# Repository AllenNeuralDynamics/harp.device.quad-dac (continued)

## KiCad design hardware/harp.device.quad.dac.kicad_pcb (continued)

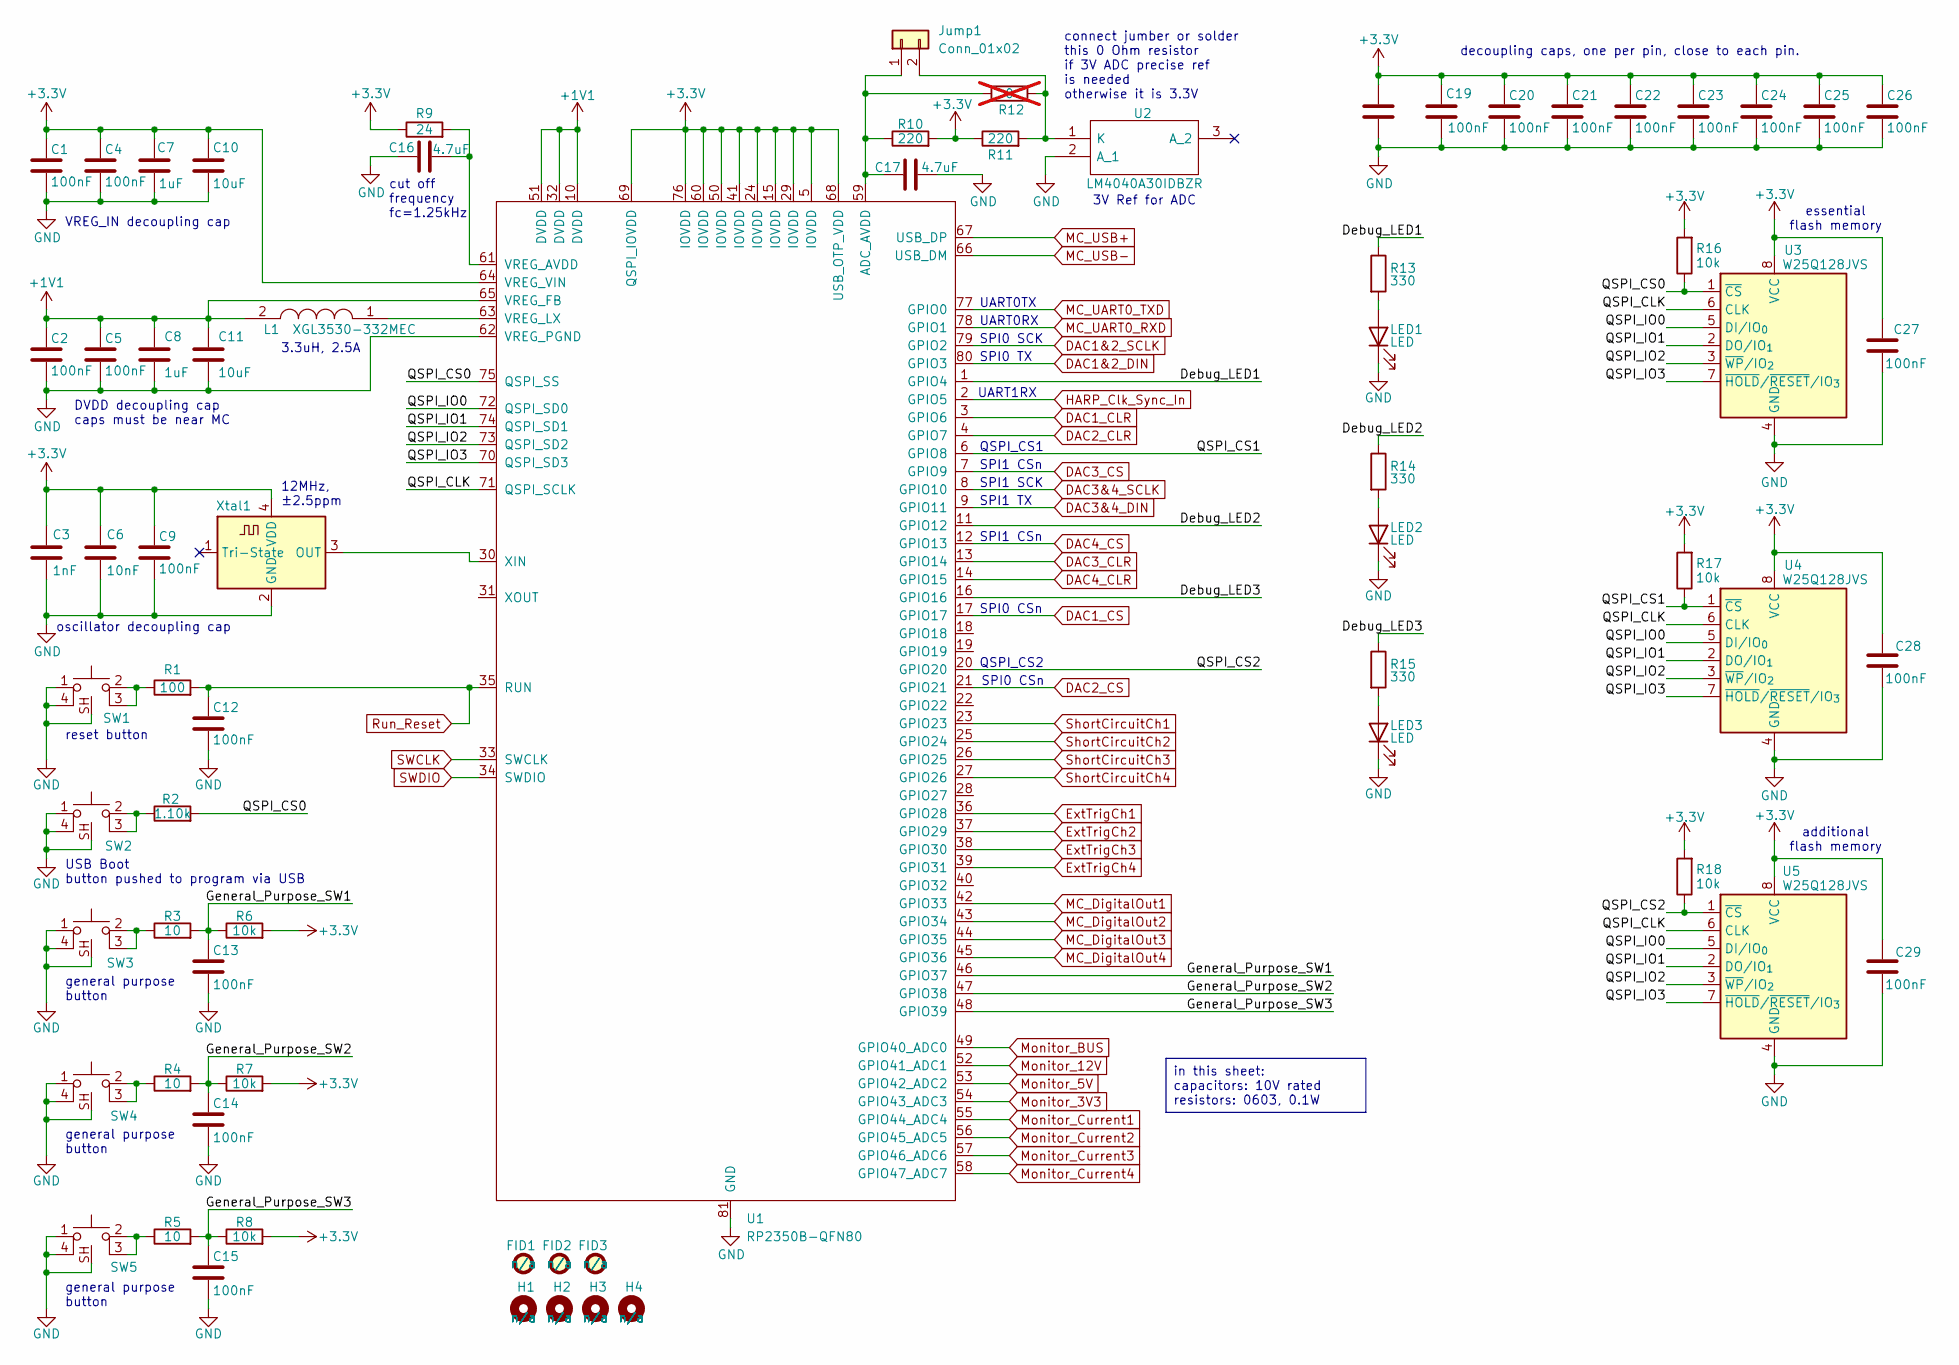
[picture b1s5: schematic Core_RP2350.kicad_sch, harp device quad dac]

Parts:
C1, C2, C4, C5, C9, C12, C13, C14, C15, C19, C20, C21, C22, C23, C24, C25, C26, C27, C28, C29: 100nF; C_0603_1608Metric; Rated Voltage 50V; Tolerance 10%; Manufacturer_Part_Number C0603C104K5RACTU
C3: 1nF; C_0603_1608Metric; Rated Voltage 50V; Tolerance 10%; Manufacturer_Part_Number C0603C102K5RACTU
C6: 10nF; C_0603_1608Metric; Rated Voltage 50V; Tolerance 10%; Manufacturer_Part_Number C0603C103K5RACTU
C7, C8: 1uF; C_0603_1608Metric; Rated Voltage 50V; Tolerance 10%; Manufacturer_Part_Number C1608X7R1H105K080AB
C10, C11, C18: 10uF; C_0603_1608Metric; Rated Voltage 25V; Tolerance 10%; Manufacturer_Part_Number GRM188R61E106KA73D
C16, C17: 4.7uF; C_0603_1608Metric; Rated Voltage 35V; Tolerance 10%; Manufacturer_Part_Number C1608X5R1V475K080AC
FID1, FID2, FID3: Fiducial; Fiducial_0.5mm_Mask1mm; Manufacturer_Part_Number n/a
H1, H2, H3, H4: MountingHole_Pad; MountingHole_3.2mm_M3_DIN965; Manufacturer_Part_Number n/a
Jump1: Conn_01x02; PinHeader_1x02_P2.54mm_Vertical; MPN M20-9990246
L1: XGL3530-332MEC; XGL3530332MEC; Manufacturer_Part_Number XGL3530-332MEC
LED1, LED2, LED3: LED; LED_0603_1608Metric_Pad1.05x0.95mm_HandSolder; MPN XZCDGK53W-1VF
R1: 100; R_0603_1608Metric; Tolerance 1%; MPN AC0603FR-13100RL
R2: 1.10k; R_0603_1608Metric; Tolerance 0.1%; MPN RT0603BRD071K1L
R3, R4, R5: 10; R_0603_1608Metric; Tolerance 1%; MPN AC0603FR-1310RL
R6, R7, R8, R16, R17, R18: 10k; R_0603_1608Metric; Tolerance 0.1%; MPN RT0603BRD0710KL
R9: 24; R_0603_1608Metric; Tolerance 1%; MPN AC0603FR-0724RL
R10, R11: 220; R_0603_1608Metric; Tolerance 1%; MPN RC0603FR-07220RL
R12: 0; R_0603_1608Metric; MPN RC0603JR-070RL; not fitted
R13, R14, R15: 330; R_0603_1608Metric; Tolerance 1%; MPN RC0603FR-07330RL
SW1, SW2, SW3, SW4, SW5: SW_Push_1P1T-SH_NO_Vertical_Wuerth_WS-TASV; MPN 435451019820
U1: RP2350B-QFN80; RP2350B_QFN-80_EP_10.573x10.573_Pitch0.4mm; MPN SC1510-A4
U2: LM4040A30IDBZR; SOT95P237X112-3N; Manufacturer_Part_Number LM4040A30IDBZR; Mouser Part Number 595-LM4040A30IDBZR
U3, U4, U5: W25Q128JVS; SOIC-8_5.3x5.3mm_P1.27mm
Xtal1: ECS-TXO-2016; Crystal_SMD_2016-4Pin_2.0x1.6mm; Tolerance ±2.5ppm; MPN ECS-TXO-2016-33-120-TR

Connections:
+1V1: C2.2, C5.2, C8.1, C11.1, L1.2, U1.10 (DVDD), U1.32 (DVDD), U1.51 (DVDD), U1.65 (VREG_FB)
+3.3V: C1.2, C3.2, C4.2, C6.2, C7.1, C9.2, C10.1, C18.1, C19.2, C20.2, C21.2, C22.2, C23.2, C24.2, C25.2, C26.2, C27.2, C28.2, C29.2, R6.2, R7.2, R8.2, R9.1, R10.2, R11.1, R16.2, R17.2, R18.2, U1.5 (IOVDD), U1.15 (IOVDD), U1.24 (IOVDD), U1.29 (IOVDD), U1.41 (IOVDD), U1.50 (IOVDD), U1.60 (IOVDD), U1.64 (VREG_VIN), U1.68 (USB_OTP_VDD), U1.69 (QSPI_IOVDD), U1.76 (IOVDD), U3.8 (VCC), U4.8 (VCC), U5.8 (VCC), Xtal1.4 (VDD); also elsewhere on the board
/Core_RP2350/Debug_LED1: R13.1, U1.1 (GPIO4)
/Core_RP2350/Debug_LED2: R14.1, U1.11 (GPIO12)
/Core_RP2350/Debug_LED3: R15.1, U1.16 (GPIO16)
/Core_RP2350/General_Purpose_SW1: C13.2, R3.2, R6.1, U1.46 (GPIO37)
/Core_RP2350/General_Purpose_SW2: C14.2, R4.2, R7.1, U1.47 (GPIO38)
/Core_RP2350/General_Purpose_SW3: C15.2, R5.2, R8.1, U1.48 (GPIO39)
/Core_RP2350/QSPI_CLK: U1.71 (QSPI_SCLK), U3.6 (CLK), U4.6 (CLK), U5.6 (CLK)
/Core_RP2350/QSPI_CS0: R2.2, R16.1, U1.75 (QSPI_SS), U3.1 (~CS)
/Core_RP2350/QSPI_CS1: R17.1, U1.6 (GPIO8), U4.1 (~CS)
/Core_RP2350/QSPI_CS2: R18.1, U1.20 (GPIO20), U5.1 (~CS)
/Core_RP2350/QSPI_IO0: U1.72 (QSPI_SD0), U3.5 (DI/IO_{0}), U4.5 (DI/IO_{0}), U5.5 (DI/IO_{0})
/Core_RP2350/QSPI_IO1: U1.74 (QSPI_SD1), U3.2 (DO/IO_{1}), U4.2 (DO/IO_{1}), U5.2 (DO/IO_{1})
/Core_RP2350/QSPI_IO2: U1.73 (QSPI_SD2), U3.3 (~WP/IO_{2}), U4.3 (~WP/IO_{2}), U5.3 (~WP/IO_{2})
/Core_RP2350/QSPI_IO3: U1.70 (QSPI_SD3), U3.7 (~HOLD/~RESET/IO_{3}), U4.7 (~HOLD/~RESET/IO_{3}), U5.7 (~HOLD/~RESET/IO_{3})
DAC1&2_DIN: U1.80 (GPIO3); also elsewhere on the board
DAC1&2_SCLK: U1.79 (GPIO2); also elsewhere on the board
DAC1_CLR: U1.3 (GPIO6); also elsewhere on the board
DAC1_CS: U1.17 (GPIO17); also elsewhere on the board
DAC2_CLR: U1.4 (GPIO7); also elsewhere on the board
DAC2_CS: U1.21 (GPIO21); also elsewhere on the board
DAC3&4_DIN: U1.9 (GPIO11); also elsewhere on the board
DAC3&4_SCLK: U1.8 (GPIO10); also elsewhere on the board
DAC3_CLR: U1.13 (GPIO14); also elsewhere on the board
DAC3_CS: U1.7 (GPIO9); also elsewhere on the board
DAC4_CLR: U1.14 (GPIO15); also elsewhere on the board
DAC4_CS: U1.12 (GPIO13); also elsewhere on the board
ExtTrigCh1: U1.36 (GPIO28); also elsewhere on the board
ExtTrigCh2: U1.37 (GPIO29); also elsewhere on the board
ExtTrigCh3: U1.38 (GPIO30); also elsewhere on the board
ExtTrigCh4: U1.39 (GPIO31); also elsewhere on the board
GND: C1.1, C2.1, C3.1, C4.1, C5.1, C6.1, C7.2, C8.2, C9.1, C10.2, C11.2, C12.1, C13.1, C14.1, C15.1, C16.1, C17.2, C18.2, C19.1, C20.1, C21.1, C22.1, C23.1, C24.1, C25.1, C26.1, C27.1, C28.1, C29.1, LED1.1 (K), LED2.1 (K), LED3.1 (K), SW1.1, SW1.4, SW1.SH, SW2.1, SW2.4, SW2.SH, SW3.1, SW3.4, SW3.SH, SW4.1, SW4.4, SW4.SH, SW5.1, SW5.4, SW5.SH, U1.62 (VREG_PGND), U1.81 (GND), U2.2 (A_1), U3.4 (GND), U4.4 (GND), U5.4 (GND), Xtal1.2 (GND); also elsewhere on the board
HARP_Clk_Sync_In: U1.2 (GPIO5); also elsewhere on the board
MC_DigitalOut1: U1.42 (GPIO33); also elsewhere on the board
MC_DigitalOut2: U1.43 (GPIO34); also elsewhere on the board
MC_DigitalOut3: U1.44 (GPIO35); also elsewhere on the board
MC_DigitalOut4: U1.45 (GPIO36); also elsewhere on the board
MC_UART0_RXD: U1.78 (GPIO1); also elsewhere on the board
MC_UART0_TXD: U1.77 (GPIO0); also elsewhere on the board
MC_USB+: U1.67 (USB_DP); also elsewhere on the board
MC_USB-: U1.66 (USB_DM); also elsewhere on the board
Monitor_3V3: U1.54 (GPIO43_ADC3); also elsewhere on the board
Monitor_5V: U1.53 (GPIO42_ADC2); also elsewhere on the board
Monitor_12V: U1.52 (GPIO41_ADC1); also elsewhere on the board
Monitor_BUS: U1.49 (GPIO40_ADC0); also elsewhere on the board
Monitor_Current1: U1.55 (GPIO44_ADC4); also elsewhere on the board
Monitor_Current2: U1.56 (GPIO45_ADC5); also elsewhere on the board
Monitor_Current3: U1.57 (GPIO46_ADC6); also elsewhere on the board
Monitor_Current4: U1.58 (GPIO47_ADC7); also elsewhere on the board
unnamed: C17.1, Jump1.1, R10.1, R12.1, U1.59 (ADC_AVDD)
unnamed: Jump1.2, R11.2, R12.2, U2.1 (K)
unnamed: LED1.2 (A), R13.2
unnamed: LED2.2 (A), R14.2
unnamed: LED3.2 (A), R15.2
unnamed: R1.1, SW1.2, SW1.3
unnamed: R2.1, SW2.2, SW2.3
unnamed: R3.1, SW3.2, SW3.3
unnamed: R4.1, SW4.2, SW4.3
unnamed: R5.1, SW5.2, SW5.3
unnamed: C16.2, R9.2, U1.61 (VREG_AVDD)
unnamed: L1.1, U1.63 (VREG_LX)
unnamed: U1.30 (XIN), Xtal1.3 (OUT)
Run_Reset: C12.2, R1.2, U1.35 (RUN); also elsewhere on the board
SWCLK: U1.33 (SWCLK); also elsewhere on the board
SWDIO: U1.34 (SWDIO); also elsewhere on the board
ShortCircuitCh1: U1.23 (GPIO23); also elsewhere on the board
ShortCircuitCh2: U1.25 (GPIO24); also elsewhere on the board
ShortCircuitCh3: U1.26 (GPIO25); also elsewhere on the board
ShortCircuitCh4: U1.27 (GPIO26); also elsewhere on the board

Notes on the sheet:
SPI0 CSn
decoupling caps, one per pin, close to each pin.
reset button
general purpose button
3V Ref for ADC
UART0RX
UART1RX
DVDD decoupling cap caps must be near MC
USB Boot button pushed to program via USB
SPI0 SCK
3.3uH, 2.5A
SPI1 SCK
VREG_IN decoupling cap
additional flash memory
connect jumber or solder this 0 Ohm resistor if 3V ADC precise ref is needed otherwise it is 3.3V
SPI1 CSn
essential flash memory
QSPI_CS2
cut off frequency fc=1.25kHz
SPI0 TX
SPI1 TX
oscillator decoupling cap
UART0TX
12MHz, ±2.5ppm
QSPI_CS1
in this sheet: capacitors: 10V rated resistors: 0603, 0.1W

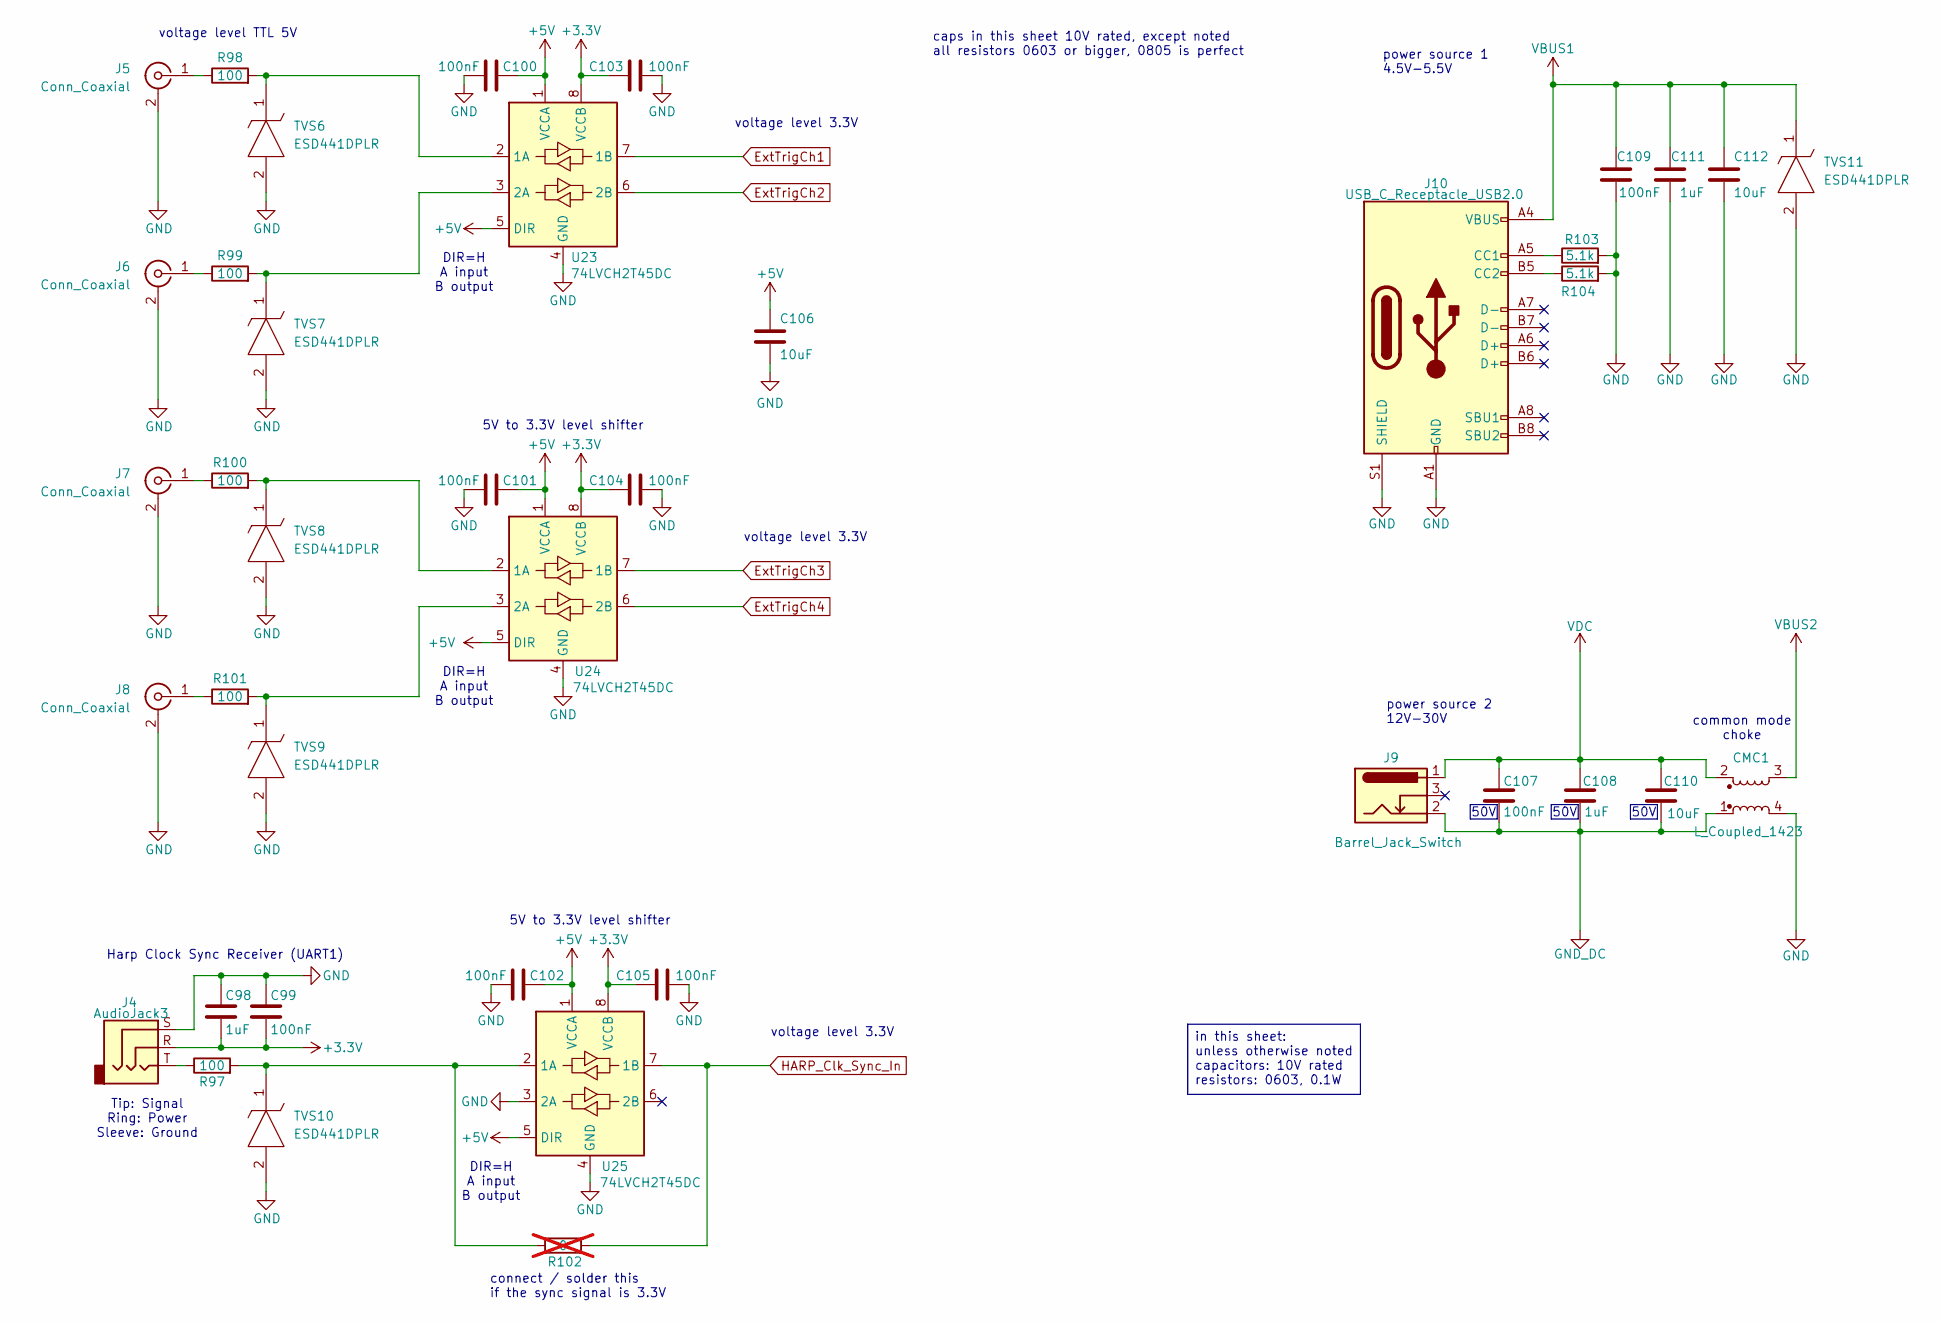
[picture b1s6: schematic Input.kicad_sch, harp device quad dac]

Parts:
C98, C108, C111: 1uF; C_0603_1608Metric; Rated Voltage 50V; Tolerance 10%; Manufacturer_Part_Number C1608X7R1H105K080AB
C99, C100, C101, C102, C103, C104, C105, C107, C109: 100nF; C_0603_1608Metric; Rated Voltage 50V; Tolerance 10%; Manufacturer_Part_Number C0603C104K5RACTU
C106, C110, C112: 10uF; C_0603_1608Metric; Rated Voltage 25V; Tolerance 10%; Manufacturer_Part_Number GRM188R61E106KA73D
CMC1: L_Coupled_1423; L_CommonModeChoke_TDKCorporation_1210
J4: AudioJack3; Jack_3.5mm_CUI_SJ-3524-SMT_Horizontal; Manufacturer_Part_Number SJ-3524-SMT-TR-BE
J5, J6, J7, J8: Conn_Coaxial; SMA_TE_Connectivity_CONSMA002-SMD-G-T_Horizontal; MPN CONSMA002-SMD-G-T
J9: Barrel_Jack_Switch; BarrelJack_CUI_PJ-102AH_Horizontal; Manufacturer_Part_Number PJ-102AH
J10: USB_C_Receptacle_USB2.0; USB_C_Receptacle_JAE_DX07S016JA1R1500; Manufacturer_Part_Number DX07S016JA1R1500
R97, R98, R99, R100, R101: 100; R_0603_1608Metric; Tolerance 1%; MPN AC0603FR-13100RL
R102: 0; R_0603_1608Metric; MPN RC0603JR-070RL; not fitted
R103, R104: 5.1k; R_0603_1608Metric; Tolerance 1%; MPN RC0603FR-075K1L
TVS6, TVS7, TVS8, TVS9, TVS10, TVS11: ESD441DPLR; Manufacturer_Part_Number ESD441DPLR; Mouser Part Number 595-ESD441DPLR
U23, U24, U25: 74LVCH2T45DC; VSSOP-8_2.3x2mm_P0.5mm

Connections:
+3.3V: C98.2, C99.1, C103.2, C104.2, C105.2, J4.R, U23.8 (VCCB), U24.8 (VCCB), U25.8 (VCCB); also elsewhere on the board
+5V: C100.1, C101.1, C102.1, C106.1, U23.1 (VCCA), U23.5 (DIR), U24.1 (VCCA), U24.5 (DIR), U25.1 (VCCA), U25.5 (DIR); also elsewhere on the board
ExtTrigCh1: U23.7 (1B); also elsewhere on the board
ExtTrigCh2: U23.6 (2B); also elsewhere on the board
ExtTrigCh3: U24.7 (1B); also elsewhere on the board
ExtTrigCh4: U24.6 (2B); also elsewhere on the board
GND: C98.1, C99.2, C100.2, C101.2, C102.2, C103.1, C104.1, C105.1, C106.2, C109.1, C111.2, C112.2, CMC1.4, J4.S, J5.2 (Ext), J6.2 (Ext), J7.2 (Ext), J8.2 (Ext), J10.A1 (GND), J10.A12 (GND), J10.B1 (GND), J10.B12 (GND), J10.S1 (SHIELD), R103.2, R104.2, TVS6.2, TVS7.2, TVS8.2, TVS9.2, TVS10.2, TVS11.2, U23.4 (GND), U24.4 (GND), U25.3 (2A), U25.4 (GND); also elsewhere on the board
GND_DC: C107.1, C108.2, C110.2, CMC1.1, J9.2
HARP_Clk_Sync_In: R102.2, U25.7 (1B); also elsewhere on the board
unnamed: J4.T, R97.1
unnamed: J5.1 (In), R98.1
unnamed: J6.1 (In), R99.1
unnamed: J7.1 (In), R100.1
unnamed: J8.1 (In), R101.1
unnamed: J10.A5 (CC1), R103.1
unnamed: J10.B5 (CC2), R104.1
unnamed: R98.2, TVS6.1, U23.2 (1A)
unnamed: R99.2, TVS7.1, U23.3 (2A)
unnamed: R100.2, TVS8.1, U24.2 (1A)
unnamed: R101.2, TVS9.1, U24.3 (2A)
unnamed: R97.2, R102.1, TVS10.1, U25.2 (1A)
VBUS1: C109.2, C111.1, C112.1, J10.A4 (VBUS), J10.A9 (VBUS), J10.B4 (VBUS), J10.B9 (VBUS), TVS11.1; also elsewhere on the board
VBUS2: CMC1.3; also elsewhere on the board
VDC: C107.2, C108.1, C110.1, CMC1.2, J9.1

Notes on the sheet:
5V to 3.3V level shifter
connect / solder this if the sync signal is 3.3V
voltage level 3.3V
caps in this sheet 10V rated, except noted all resistors 0603 or bigger, 0805 is perfect
power source 1 4.5V-5.5V
voltage level TTL 5V
common mode choke
Tip: Signal Ring: Power Sleeve: Ground
power source 2 12V-30V
DIR=H A input B output
Harp Clock Sync Receiver (UART1)
in this sheet: unless otherwise noted capacitors: 10V rated resistors: 0603, 0.1W
50V

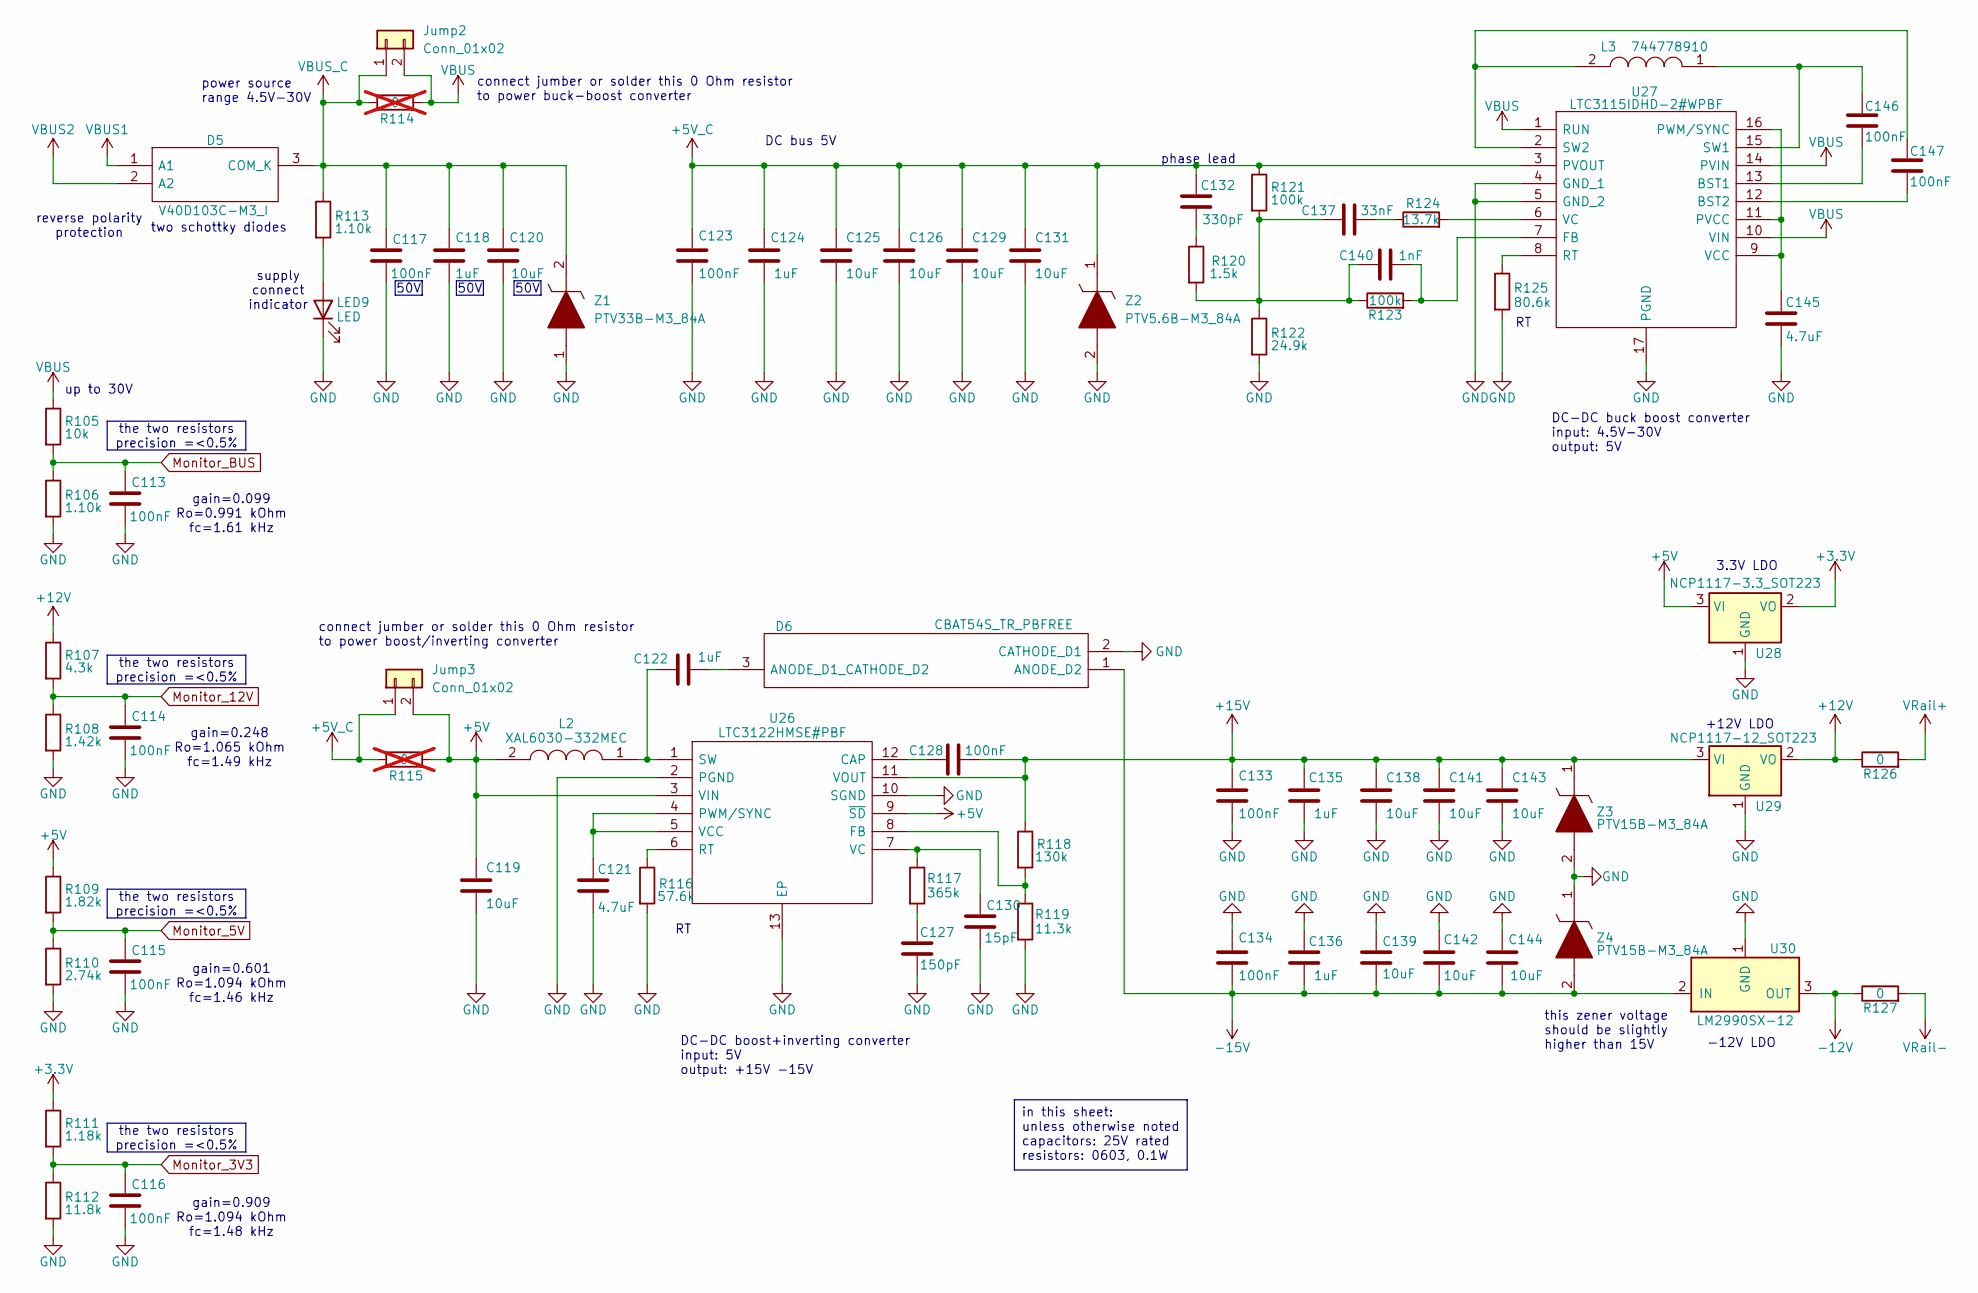
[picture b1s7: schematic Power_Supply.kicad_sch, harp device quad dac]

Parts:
C113, C114, C115, C116, C117, C123, C128, C133, C134, C146, C147: 100nF; C_0603_1608Metric; Rated Voltage 50V; Tolerance 10%; Manufacturer_Part_Number C0603C104K5RACTU
C118, C122, C124, C135, C136: 1uF; C_0603_1608Metric; Rated Voltage 50V; Tolerance 10%; Manufacturer_Part_Number C1608X7R1H105K080AB
C119, C125, C126, C129, C131, C138, C139, C141, C142, C143, C144: 10uF; C_0603_1608Metric; Rated Voltage 25V; Tolerance 10%; Manufacturer_Part_Number GRM188R61E106KA73D
C120: 10uF; C_1206_3216Metric; Rated Voltage 50V; Tolerance 10%; Manufacturer_Part_Number C3216X7R1H106K160AC
C121, C145: 4.7uF; C_0603_1608Metric; Rated Voltage 35V; Tolerance 10%; Manufacturer_Part_Number C1608X5R1V475K080AC
C127: 150pF; C_0603_1608Metric; Rated Voltage 50V; Tolerance 10%; Manufacturer_Part_Number C0603C151K5RACTU
C130: 15pF; C_0603_1608Metric; Rated Voltage 50V; Tolerance 10%; Manufacturer_Part_Number C0603C150K5RACTU
C132: 330pF; C_0603_1608Metric; Rated Voltage 50V; Tolerance 10%; Manufacturer_Part_Number C0603C331K5RACTU
C137: 33nF; C_0603_1608Metric; Rated Voltage 50V; Tolerance 10%; Manufacturer_Part_Number C0603C333K5RACTU
C140: 1nF; C_0603_1608Metric; Rated Voltage 50V; Tolerance 10%; Manufacturer_Part_Number C0603C102K5RACTU
D5: V40D103C-M3_I; V40D103CM3I; Manufacturer_Part_Number V40D103C-M3/I; Mouser Part Number 78-V40D103C-M3/I
D6: CBAT54S_TR_PBFREE; SOT95P230X109-3N; Manufacturer_Part_Number CBAT54S TR PBFREE; Mouser Part Number 610-CBAT54STR
Jump2, Jump3: Conn_01x02; PinHeader_1x02_P2.54mm_Vertical; MPN M20-9990246
L2: XAL6030-332MEC; XAL6030182MEB; Manufacturer_Part_Number XAL6030-332MEC; Mouser Part Number 994-XAL6030-332MEC
L3: 744778910; WE-PD_7332-7345_PLASTIC_BASE54; Manufacturer_Part_Number 744778910; Mouser Part Number 710-744778910
LED9: LED; LED_0603_1608Metric_Pad1.05x0.95mm_HandSolder; MPN XZCDGK53W-1VF
R105: 10k; R_0603_1608Metric; Tolerance 0.1%; MPN RT0603BRD0710KL
R106, R113: 1.10k; R_0603_1608Metric; Tolerance 0.1%; MPN RT0603BRD071K1L
R107: 4.3k; R_0603_1608Metric; Tolerance 0.1%; MPN RT0603BRD074K3L
R108: 1.42k; R_0603_1608Metric; Tolerance 0.1%; MPN RT0603BRD071K42L
R109: 1.82k; R_0603_1608Metric; Tolerance 0.1%; MPN RT0603BRD071K82L
R110: 2.74k; R_0603_1608Metric; Tolerance 0.1%; MPN RT0603BRD072K74L
R111: 1.18k; R_0603_1608Metric; Tolerance 0.1%; MPN RT0603BRD071K18L
R112: 11.8k; R_0603_1608Metric; Tolerance 0.1%; MPN RT0603BRD0711K8L
R114, R115: 0; R_0603_1608Metric; MPN RC0603JR-070RL; not fitted
R116: 57.6k; R_0603_1608Metric; Tolerance 1%; MPN RC0603FR-0757K6L
R117: 365k; R_0603_1608Metric; Tolerance 1%; MPN RC0603FR-07365KL
R118: 130k; R_0603_1608Metric; Tolerance 1%; MPN AC0603FR-07130KL
R119: 11.3k; R_0603_1608Metric; Tolerance 1%; MPN RC0603FR-0711K3L
R120: 1.5k; R_0603_1608Metric; Tolerance 1%; MPN RC0603FR-071K5L
R121, R123: 100k; R_0603_1608Metric; Tolerance 1%; MPN RC0603FR-07100KL
R122: 24.9k; R_0603_1608Metric; Tolerance 1%; MPN RC0603FR-0724K9L
R124: 13.7k; R_0603_1608Metric; Tolerance 1%; MPN AC0603FR-0713K7L
R125: 80.6k; R_0603_1608Metric; Tolerance 1%; MPN RC0603FR-0780K6L
R126, R127: 0; R_0603_1608Metric; MPN RC0603JR-070RL
U26: LTC3122HMSE#PBF; SOP65P490X110-13N; Manufacturer_Part_Number LTC3122HMSE#PBF; Mouser Part Number 584-LTC3122HMSE#PBF
U27: LTC3115IDHD-2#WPBF; SON50P400X500X80-17N-D; Manufacturer_Part_Number LTC3115IDHD-2#WPBF
U28: NCP1117-3.3_SOT223; SOT-223-3_TabPin2
U29: NCP1117-12_SOT223; SOT-223-3_TabPin2
U30: LM2990SX-12; KTT0003B
Z1: PTV33B-M3_84A; PTV47BM384A; Manufacturer_Part_Number PTV33B-M3/84A; Mouser Part Number 625-PTV33B-M3/84A
Z2: PTV5.6B-M3_84A; PTV47BM384A; Manufacturer_Part_Number PTV5.6B-M3/84A; Mouser Part Number 625-PTV5.6B-M3/84A
Z3, Z4: PTV15B-M3_84A; PTV47BM384A; Manufacturer_Part_Number PTV15B-M3/84A; Mouser Part Number 625-PTV15B-M3/84A

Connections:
+3.3V: R111.1, U28.2 (VO); also elsewhere on the board
+5V: C119.1, Jump3.2, L2.2, R109.1, R115.2, U26.3 (VIN), U26.9 (~SD), U28.3 (VI); also elsewhere on the board
+5V_C: C123.1, C124.1, C125.1, C126.1, C129.1, C131.1, C132.1, Jump3.1, R115.1, R121.1, U27.3 (PVOUT), Z2.1
+12V: R107.1, R126.1, U29.2 (VO)
+15V: C128.1, C133.1, C135.1, C138.1, C141.1, C143.1, R118.1, U26.11 (VOUT), U29.3 (VI), Z3.1
-12V: R127.1, U30.3 (OUT)
-15V: C134.2, C136.2, C139.2, C142.2, C144.2, D6.1 (ANODE_D2), U30.2 (IN), U30.4 (IN), U30.5 (IN), U30.6 (IN), Z4.2
GND: C113.1, C114.1, C115.1, C116.1, C117.1, C118.2, C119.2, C120.2, C121.2, C123.2, C124.2, C125.2, C126.2, C127.1, C129.2, C130.1, C131.2, C133.2, C134.1, C135.2, C136.1, C138.2, C139.1, C141.2, C142.1, C143.2, C144.1, C145.2, D6.2 (CATHODE_D1), LED9.1 (K), R106.2, R108.2, R110.2, R112.2, R116.2, R119.2, R122.2, R125.2, U26.2 (PGND), U26.10 (SGND), U26.13 (EP), U27.4 (GND_1), U27.5 (GND_2), U27.17 (PGND), U28.1 (GND), U29.1 (GND), U30.1 (GND), Z1.1, Z2.2, Z3.2, Z4.1; also elsewhere on the board
Monitor_3V3: C116.2, R111.2, R112.1; also elsewhere on the board
Monitor_5V: C115.2, R109.2, R110.1; also elsewhere on the board
Monitor_12V: C114.2, R107.2, R108.1; also elsewhere on the board
Monitor_BUS: C113.2, R105.2, R106.1; also elsewhere on the board
unnamed: C127.2, R117.2
unnamed: C132.2, R120.1
unnamed: C137.1, R124.1
unnamed: C137.2, C140.2, R120.2, R121.2, R122.1, R123.1
unnamed: C122.2, D6.3 (ANODE_D1_CATHODE_D2)
unnamed: LED9.2 (A), R113.2
unnamed: C128.2, U26.12 (CAP)
unnamed: R118.2, R119.1, U26.8 (FB)
unnamed: C121.1, U26.4 (PWM/SYNC), U26.5 (VCC)
unnamed: R116.1, U26.6 (RT)
unnamed: C122.1, L2.1, U26.1 (SW)
unnamed: C130.2, R117.1, U26.7 (VC)
unnamed: C146.1, U27.13 (BST1)
unnamed: C147.1, U27.12 (BST2)
unnamed: C140.1, R123.2, U27.7 (FB)
unnamed: C145.1, U27.9 (VCC), U27.11 (PVCC), U27.16 (PWM/SYNC)
unnamed: R125.1, U27.8 (RT)
unnamed: C146.2, L3.1, U27.15 (SW1)
unnamed: C147.2, L3.2, U27.2 (SW2)
unnamed: R124.2, U27.6 (VC)
VBUS: Jump2.2, R105.1, R114.2, U27.1 (RUN), U27.10 (VIN), U27.14 (PVIN)
VBUS1: D5.1 (A1); also elsewhere on the board
VBUS2: D5.2 (A2); also elsewhere on the board
VBUS_C: C117.2, C118.1, C120.1, D5.3 (COM_K), Jump2.1, R113.1, R114.1, Z1.2
VRail+: R126.2; also elsewhere on the board
VRail-: R127.2; also elsewhere on the board

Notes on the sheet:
this zener voltage should be slightly higher than 15V
supply connect indicator
+12V LDO
up to 30V
-12V LDO
3.3V LDO
phase lead
gain=0.909 Ro=1.094 kOhm fc=1.48 kHz
reverse polarity protection
DC-DC buck boost converter input: 4.5V-30V output: 5V
two schottky diodes
gain=0.601 Ro=1.094 kOhm fc=1.46 kHz
gain=0.248 Ro=1.065 kOhm fc=1.49 kHz
connect jumber or solder this 0 Ohm resistor to power boost/inverting converter
connect jumber or solder this 0 Ohm resistor to power buck-boost converter
DC-DC boost+inverting converter input: 5V output: +15V -15V
DC bus 5V
gain=0.099 Ro=0.991 kOhm fc=1.61 kHz
power source range 4.5V-30V
in this sheet: unless otherwise noted capacitors: 25V rated resistors: 0603, 0.1W
50V
the two resistors precision =<0.5%

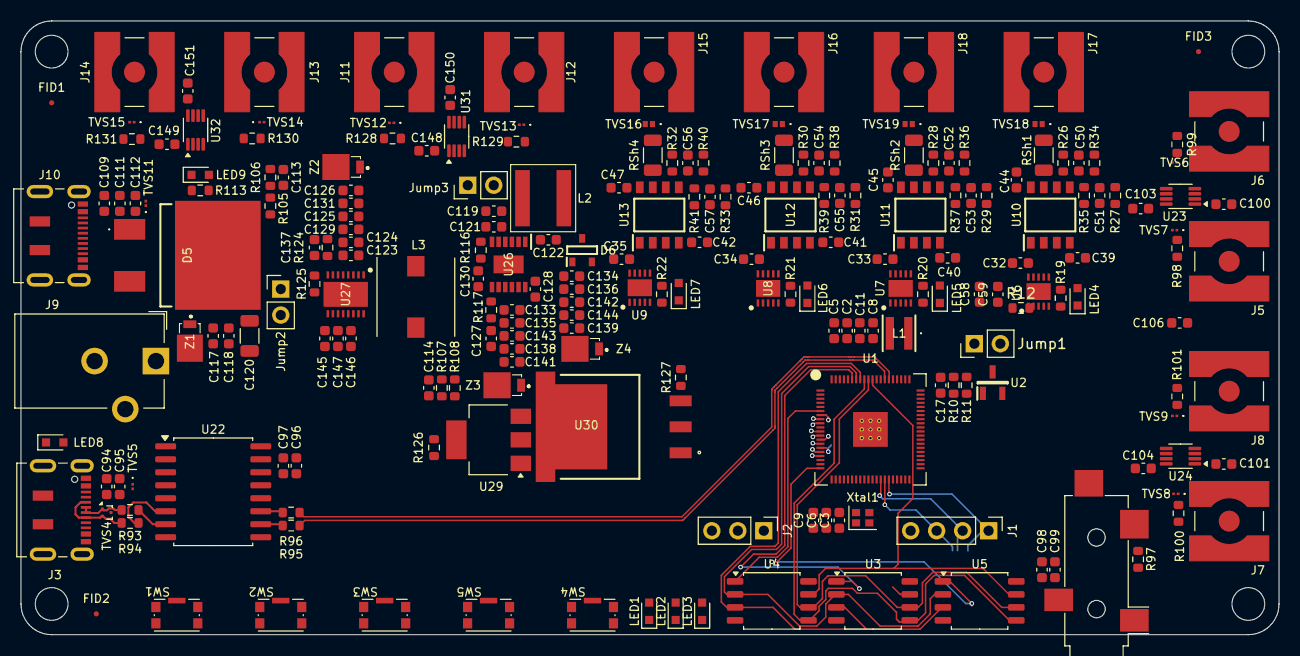
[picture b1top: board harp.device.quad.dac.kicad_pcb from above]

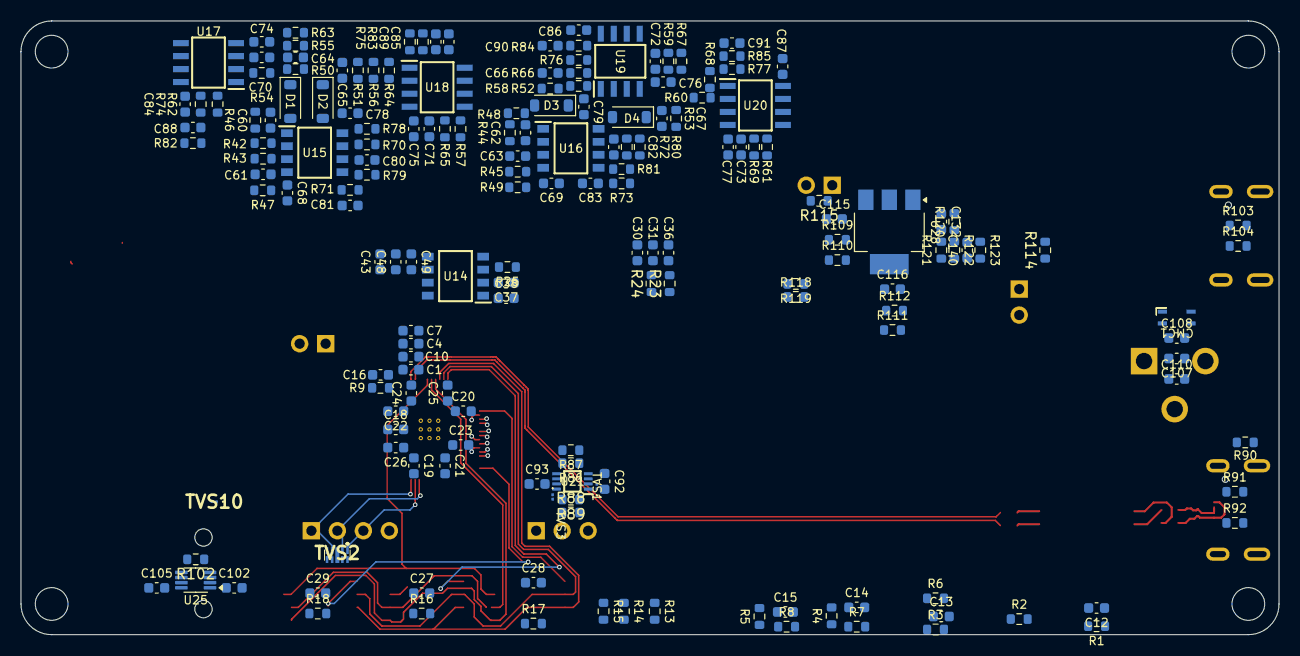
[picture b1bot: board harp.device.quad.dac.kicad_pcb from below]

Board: 4 copper layers, 123.0 x 60.0 mm, 394 parts (175 on the bottom side), 197 nets.

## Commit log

2025-08-14 adding folder structure
2025-08-20 Add Readme file
2025-08-20 Add Harp template as like as device.hobgoblin project
2025-08-20 Add submodule
2025-08-20 fix the directory in CMakeLists.txt
2025-08-23 Using HARP.device template for source file
2025-09-05 Add config.h file
2025-09-05 Update name of HARP Device
2025-09-05 Add Registers for Start and Stop each Channel
2025-09-05 Add Register for Flash Erasing
2025-09-05 Add Register for Specification Waveforms
2025-09-05 Implementation of Erasing Flash Memory Function
2025-09-06 Write 100KB of waveform on Flash Memory
2025-09-11 The final schematic has been completed, and layout preparation will now begin.
2025-09-11 Added schematic in PDF form
2025-09-13 Added caps voltage rating + block diagram
2025-09-14 The footprint assigning and reviewing have started.
2025-09-14 Modified notes about caps and resistors
2025-09-14 Updating some footprints
2025-09-17 The layout design has begun.
2025-09-23 Some improvements have been made to the layout.
2025-09-24 Jumpers and interstages connections + added zeners to supply sections + justified text
2025-09-28 The part designators have been reannotated.
2025-10-05 BOM for all capacitors and resistors is added correctly to the schematic
2025-10-06 Not necessary text is hidden + BOM on schematic
2025-10-07 BOM cont.
2025-10-13 TVS16,TVS17,TVS18,TVS19 parts have been changed from ESDSB12VLB-TP to PESD12VL1BSLAZ
2025-10-13 Rename Some nets
2025-11-03 The layout is complete, and the design is currently in the review stage.
2025-11-05 Continue BOM + enhance BOM + enhance schematic
2025-11-05 The final review has been completed, and the manufacturing files have been generated.
2025-11-11 Create interrupts every update rates times
2025-11-11 Prepare one shot and continous waveforms
